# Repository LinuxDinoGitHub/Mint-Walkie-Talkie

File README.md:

# Mint-Walkie-Talkie
An ATMega328P-powered compact walkie-talkie PCB that fits inside a mint can. Uses the NRF24L01+PA+LNA module to communicate using a custom protocol on a PCB. Range of around 1km.

## About this project
I've been thinking to make a walkie talkie since the first time I was introduced to PCB design. I have been trying since with the PCB e-ink card project, but that was a side project I never finished (maybe one day). A lot of movies show that walkie-talkies can shrink to absurdly small sizes, which I believe it can with the correct ICs and good PCB layout. But this is my first attempt at making a compact walkie-talkie module with the NRF24L01 module and ATMega328p MCU. The NRF24L01 is known for its long range, around 1km, and it is very compatible and beginner-friendly for hobbyists to use.

### Why did I make this project?
Following my last radio project, I realised I needed some walkie-talkies to match it, so I decided to make this. It is also a test of the world of electronics and how small one can make a walkie-talkie (for now, not so small yet).

### How do you use it?
Simply hold the button on the PCB/mint can, and you'll go into "transmit" mode. Release and it will go into "receive". It is essentially a half-duplex walkie-talkie. 

**Option A: Mint box outer shell**

You should have one of your own mint boxes like the following:

You will need to use a hammer & nail to cut out the holes for the speakers by using a nail to trace the outline, then cutting it out. **Tip: use the [stencil provided here](https://github.com/LinuxDinoGitHub/Mint-Walkie-Talkie/blob/main/assets/Stencil_print_in_a4.pdf) to print out and mark the traces.** More photos coming soon.

**Dimensions:**

A: 8.5mm

B: 10mm

C: 20mm

D: 3.5mm

The PTT button will need to be 3D printed ([file here](https://github.com/LinuxDinoGitHub/Mint-Walkie-Talkie/blob/main/models/button.step)) and assembled by press-fitting from the bottom (use glue to help if you punched your hole too big) to the 6mm button on the PCB trace through the mint box, using the taper to lock it in place.

**Option B: 3D printed replica mint box casing ([Link here](https://github.com/LinuxDinoGitHub/Mint-Walkie-Talkie/blob/main/models/3D_printed_case.step))**

If you don't have a mint box, you can use a 3D printed case and save yourself the hassle of manually making the holes. Print the file linked above; the button is included, assembly same as above.

## Key features
- PPT Button, half-duplex system as mentioned above
- LED signifier
- Can fit into a mint can
- Powered by a 3.7 V LiPo battery with a rechargeable battery protection module (TP4056)
- 8Ohm 1W Speaker amplified with PAM8403
- Microphone input with MAX9814

## [Schematic](https://github.com/LinuxDinoGitHub/Mint-Walkie-Talkie/tree/main/pcb)

## [PCB](https://github.com/LinuxDinoGitHub/Mint-Walkie-Talkie/tree/main/pcb)

Simple 3-layer PCB, with a ground plane for removing noise.

### First layer

### Second layer (Ground plane)

### Third layer

## 3D View

### Front

### Back

## Example use case in Mint can

## [Firmware](https://github.com/LinuxDinoGitHub/Mint-Walkie-Talkie/blob/main/firmware/mint.ino)
The firmware requires another Arduino (Uno, Mega, Nano, etc.) to program the ATMega328P. This is done with the 6 pins on the PCB (see below); for more details, check out this [Arduino article on how to program an ATMega328P](https://docs.arduino.cc/built-in-examples/arduino-isp/ArduinoToBreadboard/). All the pins you need are provided in the header pins.

## BOM
[BOM](https://github.com/LinuxDinoGitHub/Mint-Walkie-Talkie/blob/main/BOM_with_links.csv)** with links **to vendors and sources of material.
[BOM](https://github.com/LinuxDinoGitHub/Mint-Walkie-Talkie/blob/main/BOM_KiCAD_generated.csv) generated by KiCAD with components listing.
The project will cost an average of $6 per walkie-talkie, but most of the materials require bulk purchases.

## Zine page

## Credits
Thank you to the great documentation from [RF24 library](https://github.com/nRF24/RF24), a really convenient and high-speed data transfer library for the NRF24L01.

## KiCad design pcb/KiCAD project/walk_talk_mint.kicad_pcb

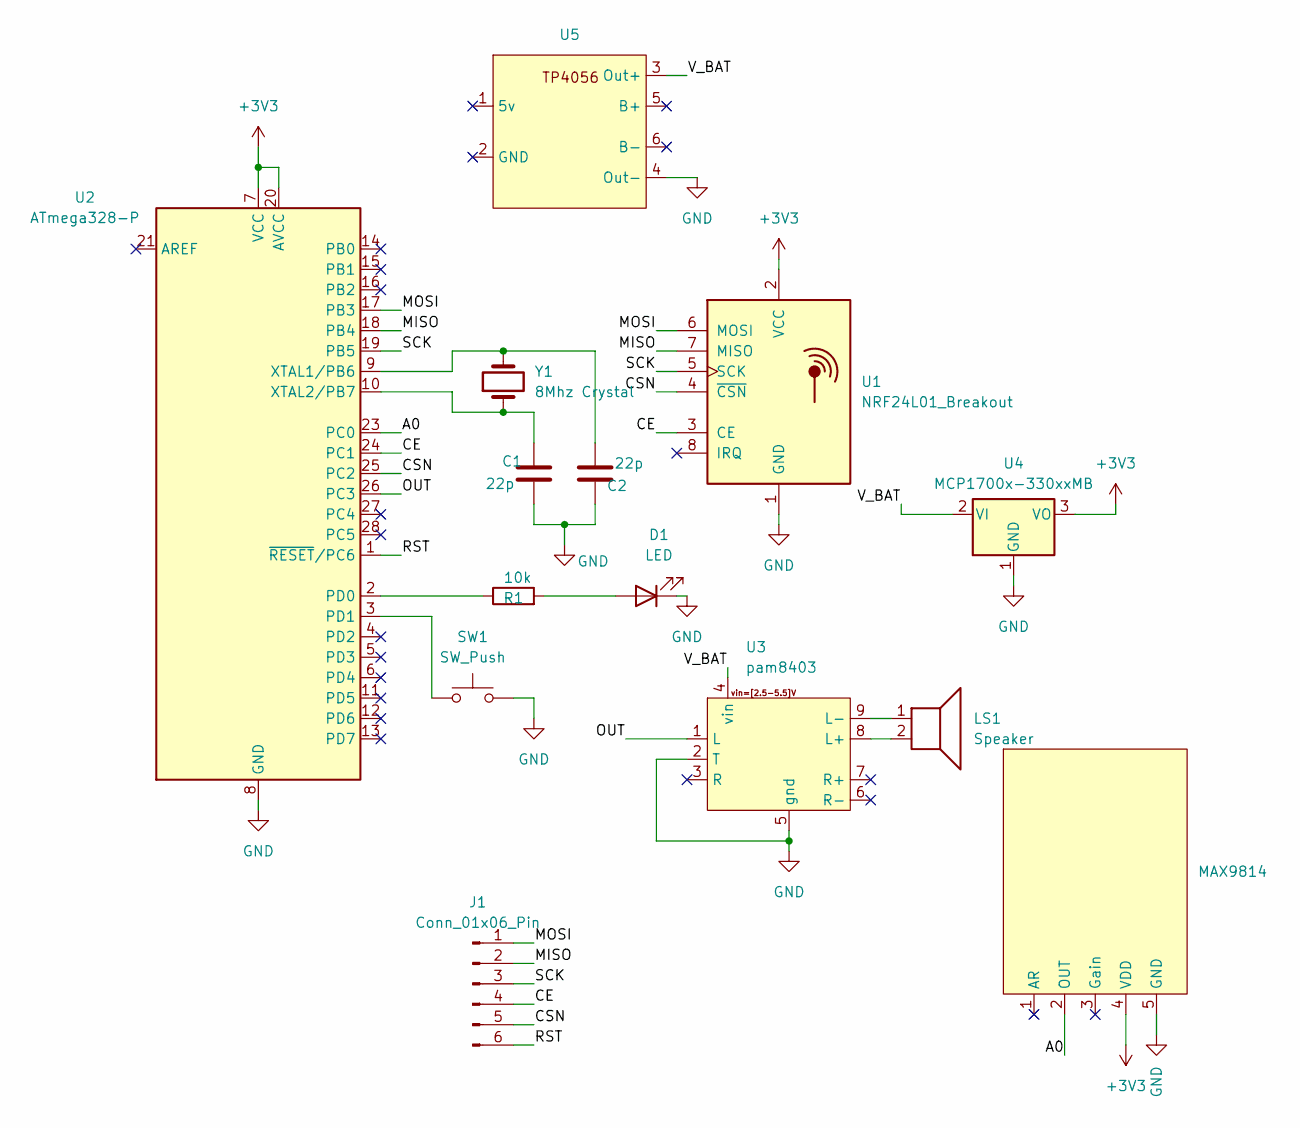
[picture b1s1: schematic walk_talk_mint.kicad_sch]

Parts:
C1, C2: 22p; C_Axial_L3.8mm_D2.6mm_P7.50mm_Horizontal
D1: LED; PinHeader_1x02_P2.54mm_Vertical
J1: Conn_01x06_Pin; PinSocket_1x06_P2.54mm_Vertical
LS1: Speaker; PinHeader_1x02_P2.54mm_Vertical
MAX9814: PinSocket_1x05_P2.54mm_Vertical
R1: 10k; R_Axial_DIN0204_L3.6mm_D1.6mm_P2.54mm_Vertical
SW1: SW_Push; SW_PUSH_6mm_H5mm
U1: NRF24L01_Breakout; nRF24L01_Breakout
U2: ATmega328-P; DIP-28_W7.62mm
U3: pam8403
U4: MCP1700x-330xxMB; SOT-89-3
U5: TP4056-18650
Y1: 8Mhz Crystal; PinHeader_1x02_P2.54mm_Vertical

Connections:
+3V3: MAX9814.4 (VDD), U1.2 (VCC), U2.7 (VCC), U2.20 (AVCC), U4.3 (VO)
/A0: MAX9814.2 (OUT), U2.23 (PC0)
/CE: J1.4, U1.3 (CE), U2.24 (PC1)
/CSN: J1.5, U1.4 (~CSN), U2.25 (PC2)
/MISO: J1.2, U1.7 (MISO), U2.18 (PB4)
/MOSI: J1.1, U1.6 (MOSI), U2.17 (PB3)
/OUT: U2.26 (PC3), U3.1 (L)
/RST: J1.6, U2.1 (~RESET/PC6)
/SCK: J1.3, U1.5 (SCK), U2.19 (PB5)
/V_BAT: U3.4 (vin), U4.2 (VI), U5.3 (Out+)
GND: C1.2, C2.1, D1.1 (K), MAX9814.5 (GND), SW1.2, U1.1 (GND), U2.8 (GND), U2.22 (GND), U3.2 (T), U3.5 (gnd), U4.1 (GND), U5.4 (Out-)
unnamed: D1.2 (A), R1.2
unnamed: R1.1, U2.2 (PD0)
unnamed: SW1.1, U2.3 (PD1)
unnamed: C2.2, U2.9 (XTAL1/PB6), Y1.2
unnamed: C1.1, U2.10 (XTAL2/PB7), Y1.1
unnamed: LS1.2, U3.8 (L+)
unnamed: LS1.1, U3.9 (L-)

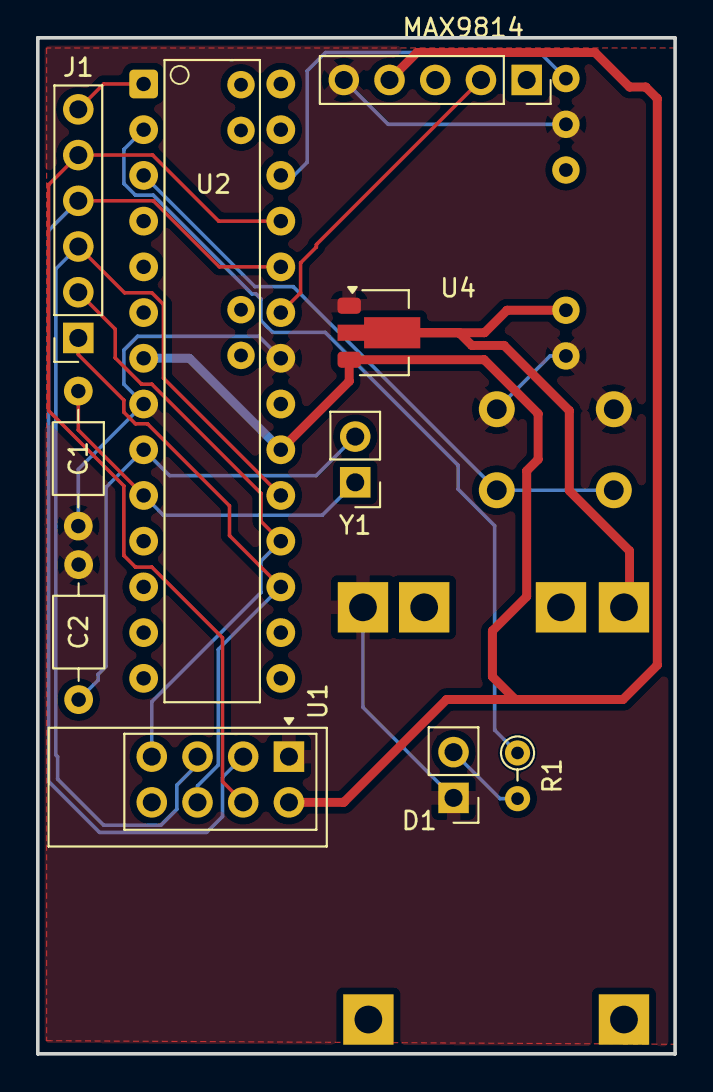
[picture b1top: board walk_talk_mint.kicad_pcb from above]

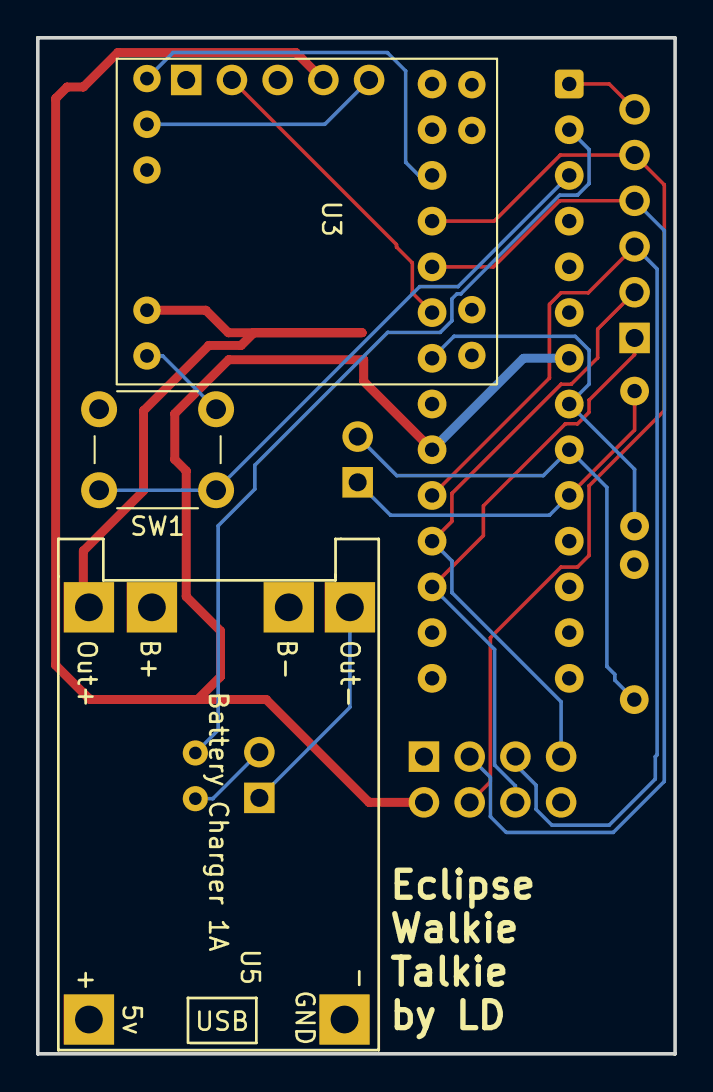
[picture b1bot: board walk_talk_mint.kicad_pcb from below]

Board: 2 copper layers, 35.4 x 56.4 mm, 13 parts (3 on the bottom side), 16 nets.

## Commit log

2026-05-28 Added pcb, assets, firmware, and BOM files
2026-05-28 Finished Zine pages
2026-05-28 updated zine
2026-05-28 Enhance README with project details and usage
    Expanded project description and added usage instructions, features, and links to firmware and schematic.
2026-05-28 Added BOM
2026-05-28 Update README with assembly instructions and image
    Added assembly notes and image reference for mint box.
2026-05-28 added shapr source file
2026-06-03 Updated pcb files formatting
2026-06-03 Revise README with assembly tips and resource links
    Updated instructions for assembly and added links to BOM and RF24 library documentation.
2026-06-03 added step files for assembly
2026-06-03 added stencil
2026-06-03 Enhance README with detailed assembly instructions
    Updated instructions and links for assembly and firmware.
2026-06-03 added fusion fiel
